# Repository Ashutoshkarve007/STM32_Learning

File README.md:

# STM32_Learning
 Learn STM32 together. 
 Create your name folder, >> create pull request.
 
#add to discord
webhook
lk

*Slave Board*

pin 1 - VCC     Modbus side
pin 2 - DO
pin 3 - CLK
pin 4 - rst*
pin 5 - GND

Master - Slave

Request Data - {slave_id, 0x06, CRC_L, CRC_H}

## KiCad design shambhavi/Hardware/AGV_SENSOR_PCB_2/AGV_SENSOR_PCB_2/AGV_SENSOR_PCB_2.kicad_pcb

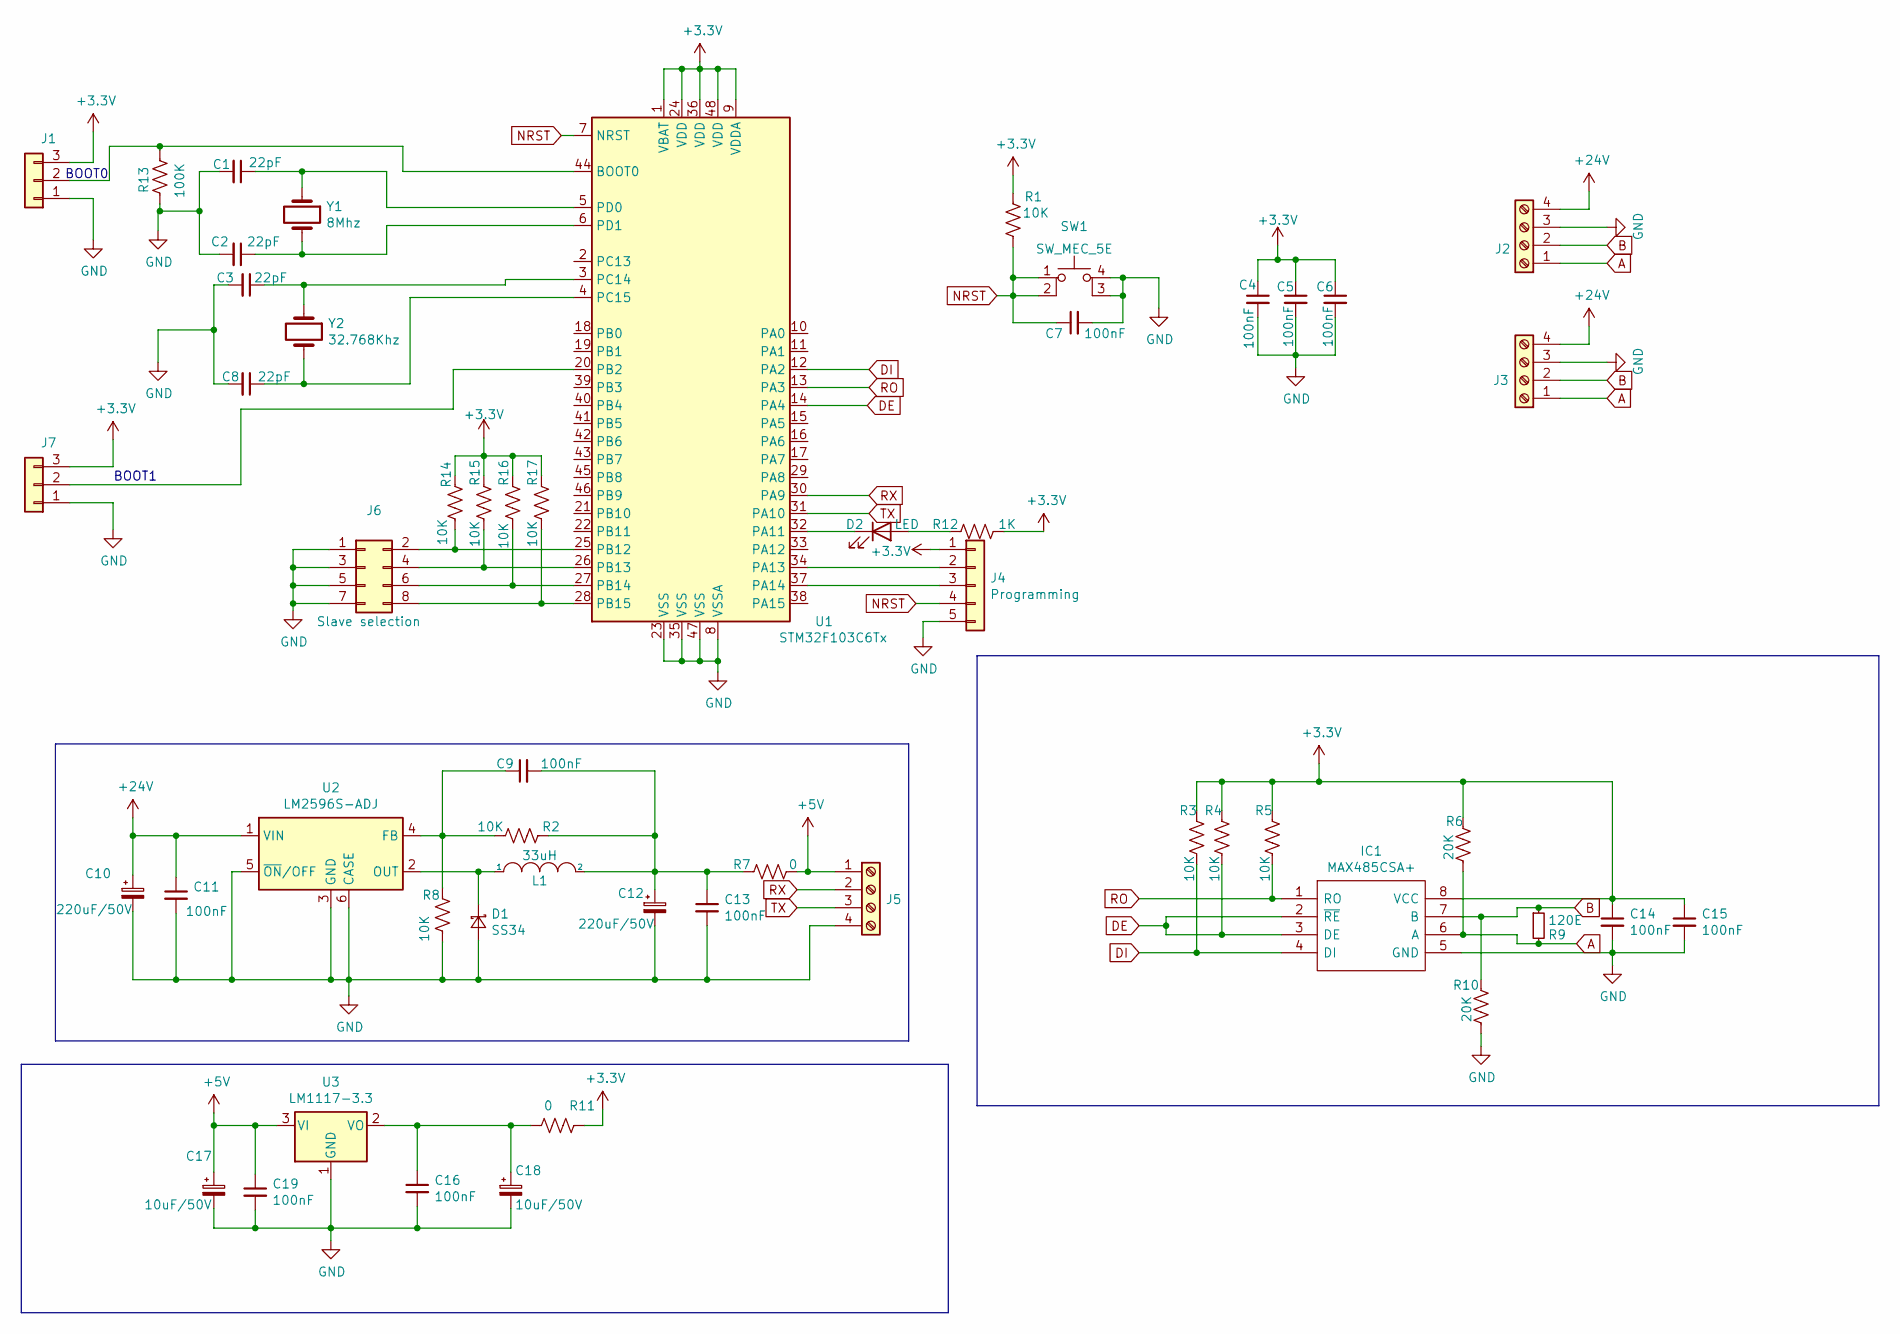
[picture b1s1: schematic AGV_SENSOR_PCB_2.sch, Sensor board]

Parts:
C1, C2, C3, C8: 22pF; C_0805_2012Metric
C4, C5, C6, C7, C9, C11, C13, C14, C15, C16, C19: 100nF; C_0805_2012Metric
C10, C12: 220uF/50V; CP_Radial_D8.0mm_P3.80mm
C17, C18: 10uF/50V; CP_Radial_D5.0mm_P2.50mm
D1: SS34; SODFL5226X100N
D2: LED; LED_0805_2012Metric
IC1: MAX485CSA+; SOIC127P600X175-8N; Manufacturer_Part_Number MAX485CSA+; Mouser Part Number 700-MAX485CSA
J1, J7: Conn_01x03; PinSocket_1x03_P2.54mm_Vertical
J2, J3, J5: Screw_Terminal_01x04; PhoenixContact_MCV_1,5_4-G-5.08_1x04_P5.08mm_Vertical
J4: Programming; PinSocket_1x05_P2.54mm_Vertical
J6: Slave selection; PinSocket_2x04_P2.54mm_Vertical
L1: 33uH; L_12x12mm_H6mm
R1, R2, R3, R4, R5, R8, R14, R15, R16, R17: 10K; R_0805_2012Metric
R6, R10: 20K; R_0805_2012Metric
R7, R11: 0; R_0805_2012Metric
R9: 120E; R_0805_2012Metric
R12: 1K; R_0805_2012Metric
R13: 100K; R_0805_2012Metric
SW1: SW_MEC_5E; SW_TH_Tactile_Omron_B3F-10xx
U1: STM32F103C6Tx; LQFP-48_7x7mm_P0.5mm
U2: LM2596S-ADJ; TO-263-5_TabPin3
U3: LM1117-3.3; SOT-223-3_TabPin2
Y1: 8Mhz; Crystal_HC49-4H_Vertical
Y2: 32.768Khz; Crystal_DS26_D2.0mm_L6.0mm_Horizontal

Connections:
+3V3: C4.1, C5.1, C6.1, C14.1, C15.1, IC1.8 (VCC), J1.3, J4.1, J7.3, R1.1, R3.1, R4.1, R5.1, R6.1, R11.1, R12.2, R14.1, R15.1, R16.1, R17.1, U1.1 (VBAT), U1.9 (VDDA), U1.24 (VDD), U1.36 (VDD), U1.48 (VDD)
+5V: C17.1, C19.1, J5.1, R7.1, U3.3 (VI)
+24V: C10.1, C11.1, J2.4, J3.4, U2.1 (VIN)
A: IC1.6 (A), J2.1, J3.1, R6.2, R9.2
B: IC1.7 (B), J2.2, J3.2, R9.1, R10.1
DE: IC1.2 (~RE), IC1.3 (DE), R4.2, U1.14 (PA4)
DI: IC1.4 (DI), R3.2, U1.12 (PA2)
GND: C1.2, C2.2, C3.2, C4.2, C5.2, C6.2, C7.2, C8.2, C10.2, C11.2, C12.2, C13.2, C14.2, C15.2, C16.2, C17.2, C18.2, C19.2, D1.1 (A), IC1.5 (GND), J1.1, J2.3, J3.3, J4.5, J5.4, J6.1, J6.3, J6.5, J6.7, J7.1, R8.1, R10.2, R13.1, SW1.3 (K), SW1.4 (A), U1.8 (VSSA), U1.23 (VSS), U1.35 (VSS), U1.47 (VSS), U2.3 (GND), U2.5 (~ON~/OFF), U2.6 (CASE), U3.1 (GND)
NRST: C7.1, J4.4, R1.2, SW1.1, SW1.2, U1.7 (NRST)
unnamed: C1.1, U1.5 (PD0), Y1.1
unnamed: C2.1, U1.6 (PD1), Y1.2
unnamed: C3.1, U1.3 (PC14), Y2.1
unnamed: C8.1, U1.4 (PC15), Y2.2
unnamed: C9.1, R2.2, R8.2, U2.4 (FB)
unnamed: C9.2, C12.1, C13.1, L1.2, R2.1, R7.2
unnamed: C16.1, C18.1, R11.2, U3.2 (VO)
unnamed: D1.2 (K), L1.1, U2.2 (OUT)
unnamed: D2.1 (K), U1.32 (PA11)
unnamed: D2.2 (A), R12.1
unnamed: J1.2, R13.2, U1.44 (BOOT0)
unnamed: J4.2, U1.34 (PA13)
unnamed: J4.3, U1.37 (PA14)
unnamed: J6.2, R14.2, U1.25 (PB12)
unnamed: J6.4, R15.2, U1.26 (PB13)
unnamed: J6.6, R16.2, U1.27 (PB14)
unnamed: J6.8, R17.2, U1.28 (PB15)
unnamed: J7.2, U1.20 (PB2)
RO: IC1.1 (RO), R5.2, U1.13 (PA3)
RX: J5.2, U1.30 (PA9)
TX: J5.3, U1.31 (PA10)

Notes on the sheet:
BOOT1
BOOT0

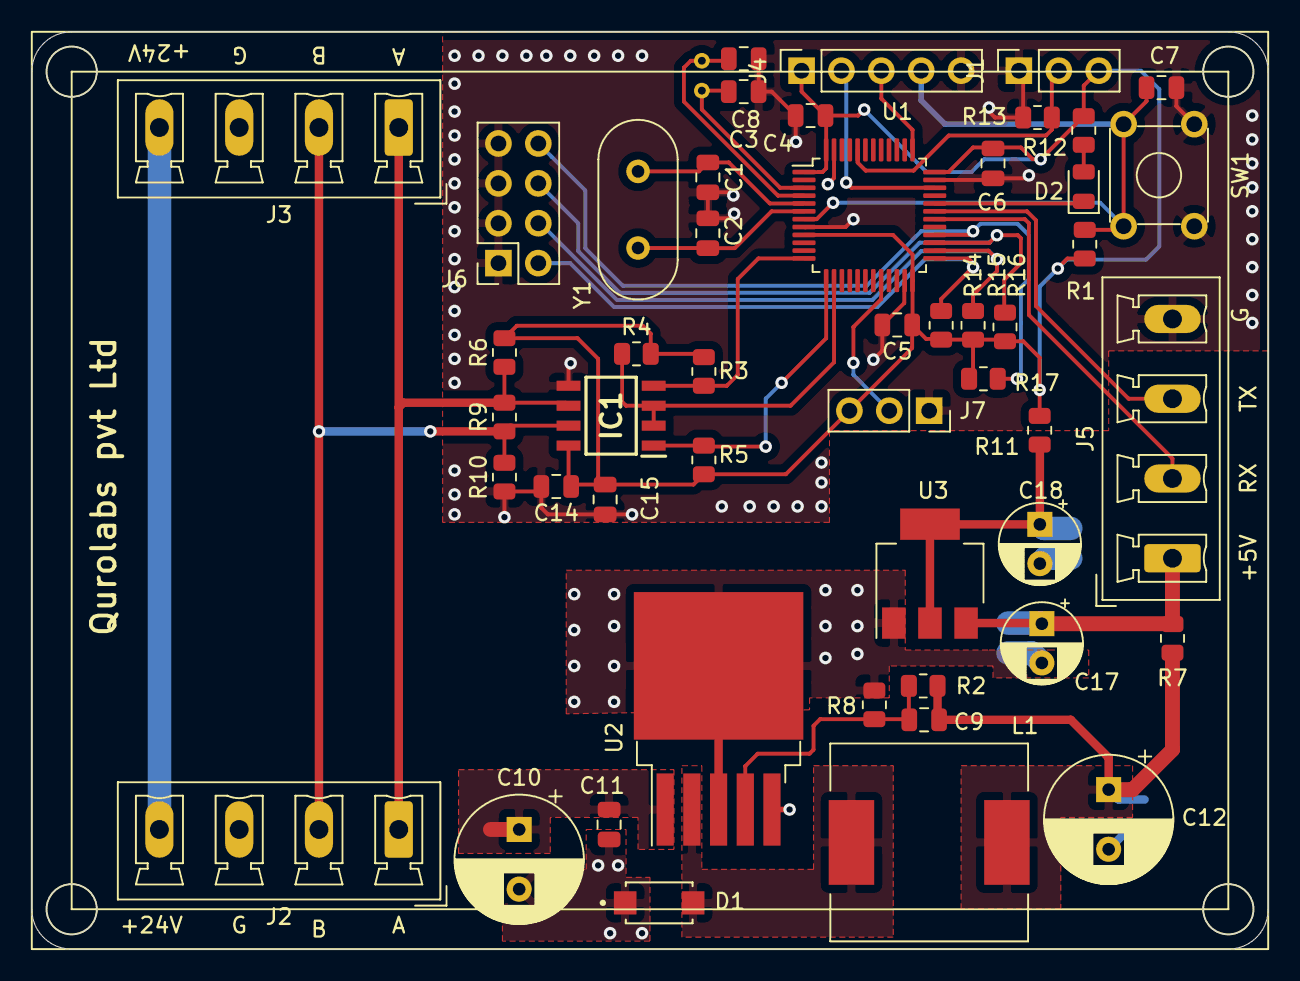
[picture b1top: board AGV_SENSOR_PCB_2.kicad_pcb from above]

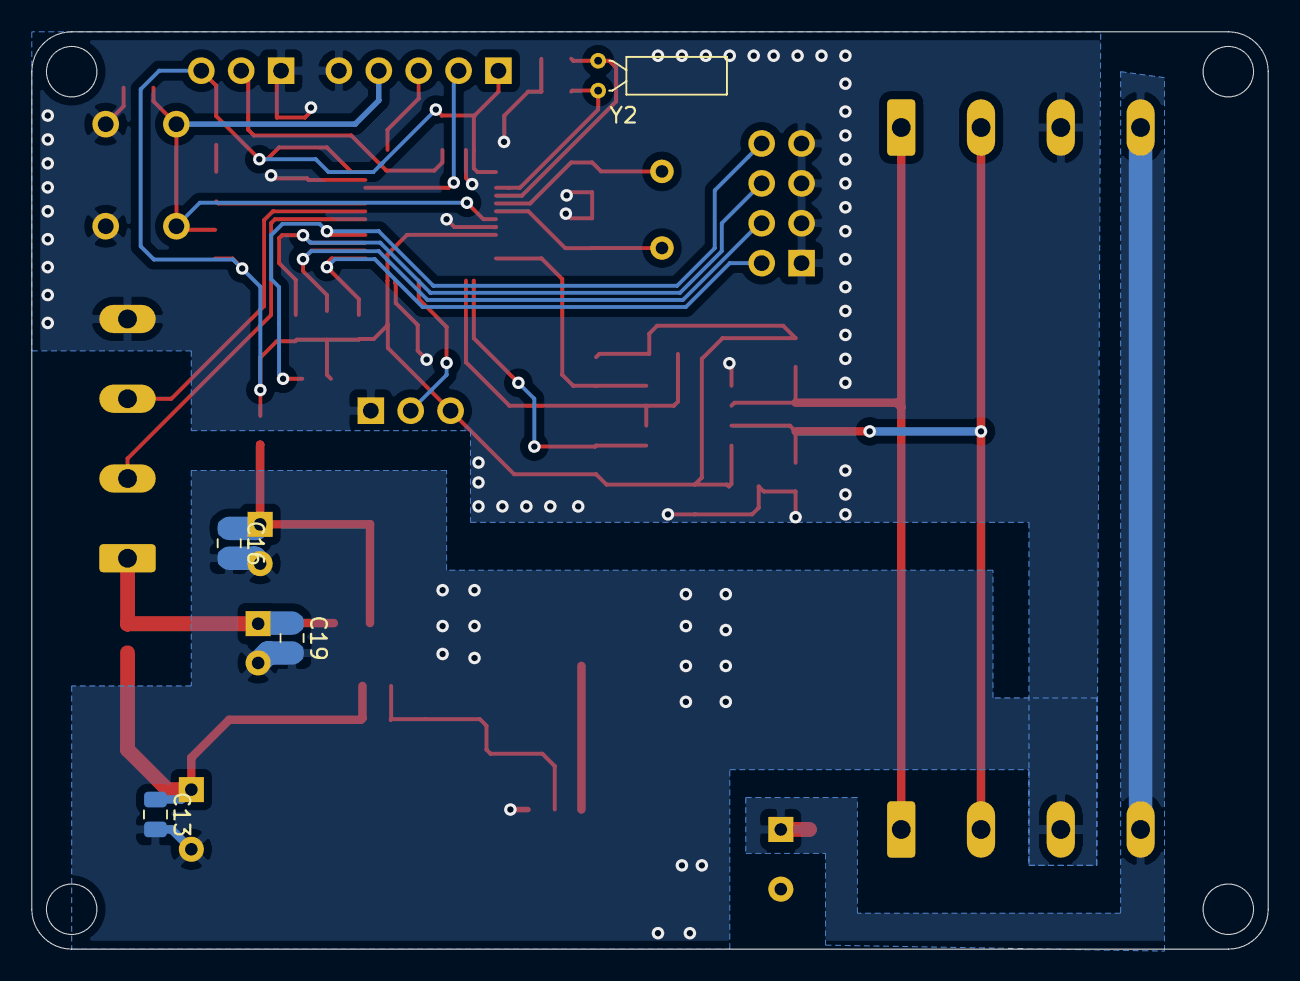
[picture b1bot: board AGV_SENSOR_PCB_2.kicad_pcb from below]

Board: 2 copper layers, 78.7 x 58.4 mm, 53 parts (4 on the bottom side), 30 nets.

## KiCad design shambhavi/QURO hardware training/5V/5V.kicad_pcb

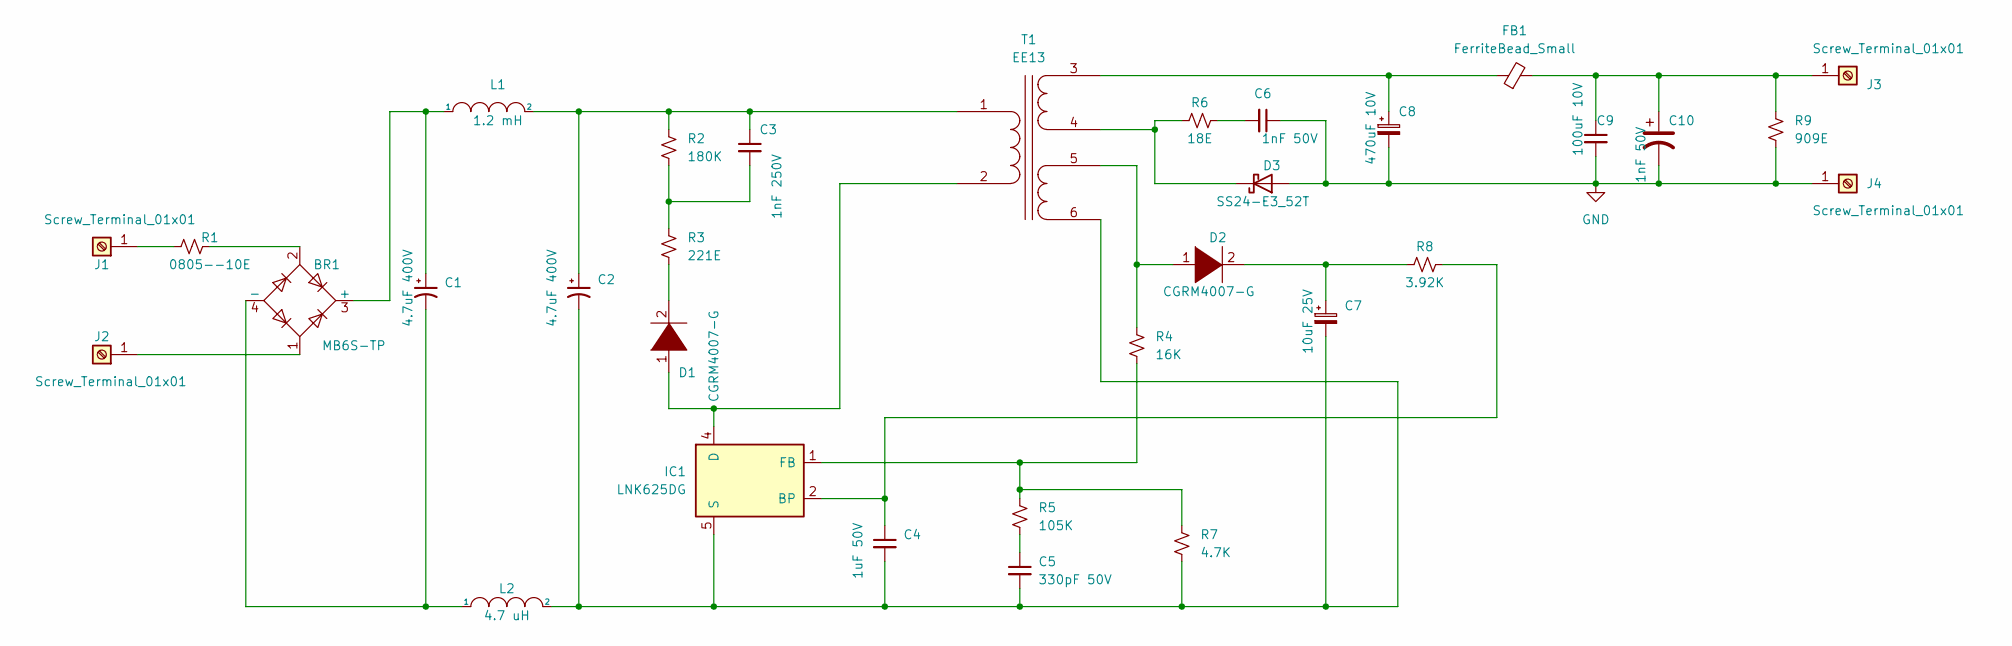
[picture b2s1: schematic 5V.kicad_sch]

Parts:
BR1: MB6S-TP; TO-269AA
C1: 4.7uF 400V; CP_Radial_D8.0mm_P3.80mm
C2: 4.7uF 400V; CP_Radial_D8.0mm_P3.50mm
C3: 1nF 250V; C_Radial_D8.0mm_H7.0mm_P3.50mm
C4: 1uF 50V; C_Radial_D8.0mm_H7.0mm_P3.50mm
C5: 330pF 50V; C_Radial_D8.0mm_H7.0mm_P3.50mm
C6: 1nF 50V; C_Radial_D8.0mm_H7.0mm_P3.50mm
C7: 10uF 25V; CP_Radial_D8.0mm_P3.50mm
C8: 470uF 10V; CP_Radial_D8.0mm_P3.50mm
C9: 100uF 10V; C_Radial_D8.0mm_H7.0mm_P3.50mm
C10: 1nF 50V; CP_Radial_D8.0mm_P3.80mm
D1, D2: CGRM4007-G; D_MiniMELF
D3: SS24-E3_52T; D_MiniMELF
FB1: FerriteBead_Small; L_0603_1608Metric
IC1: LNK625DG; PowerIntegrations_SO-8C
J1, J2, J3, J4: Screw_Terminal_01x01; TerminalBlock_MetzConnect_360272_1x01_Horizontal_ScrewM2.6
L1: 1.2 mH; L_Radial_D8.7mm_P5.00mm_Fastron_07HCP
L2: 4.7 uH; L_0805_2012Metric
R1: 0805--10E; R_0805_2012Metric_Pad1.20x1.40mm_HandSolder
R2: 180K; R_0805_2012Metric
R3: 221E; R_0805_2012Metric
R4: 16K; R_0815_2038Metric
R5: 105K; R_0815_2038Metric
R6: 18E; R_0815_2038Metric
R7: 4.7K; R_0815_2038Metric
R8: 3.92K; R_0815_2038Metric
R9: 909E; R_0815_2038Metric
T1: EE13; Transformer_Wuerth_750343373

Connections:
GND: C6.1, C8.2, C9.2, C10.2, D3.2 (A), J4.1, R9.2
unnamed: BR1.1, J2.1
unnamed: BR1.2, R1.2
unnamed: BR1.3 (+), C1.1, L1.1
unnamed: BR1.4 (-), C1.2, L2.1
unnamed: C2.1, C3.1, L1.2, R2.1, T1.1 (AA)
unnamed: C2.2, C4.2, C5.2, C7.2, IC1.5 (S), IC1.6 (S), IC1.7 (S), IC1.8 (S), L2.2, R7.2, T1.6 (SD)
unnamed: C5.1, R5.2
unnamed: C6.2, R6.2
unnamed: C8.1, FB1.1, T1.3 (SA)
unnamed: D1.1 (K), IC1.4 (D), T1.2 (AB)
unnamed: D1.2 (A), R3.2
unnamed: C7.1, D2.2 (A), R8.1
unnamed: IC1.1 (FB), R4.2, R5.1, R7.1
unnamed: C4.1, IC1.2 (BP), R8.2
unnamed: C9.1, C10.1, FB1.2, J3.1, R9.1
unnamed: J1.1, R1.1
unnamed: C3.2, R2.2, R3.1
unnamed: D2.1 (K), R4.1, T1.5 (SC)
unnamed: D3.1 (K), R6.1, T1.4 (SB)

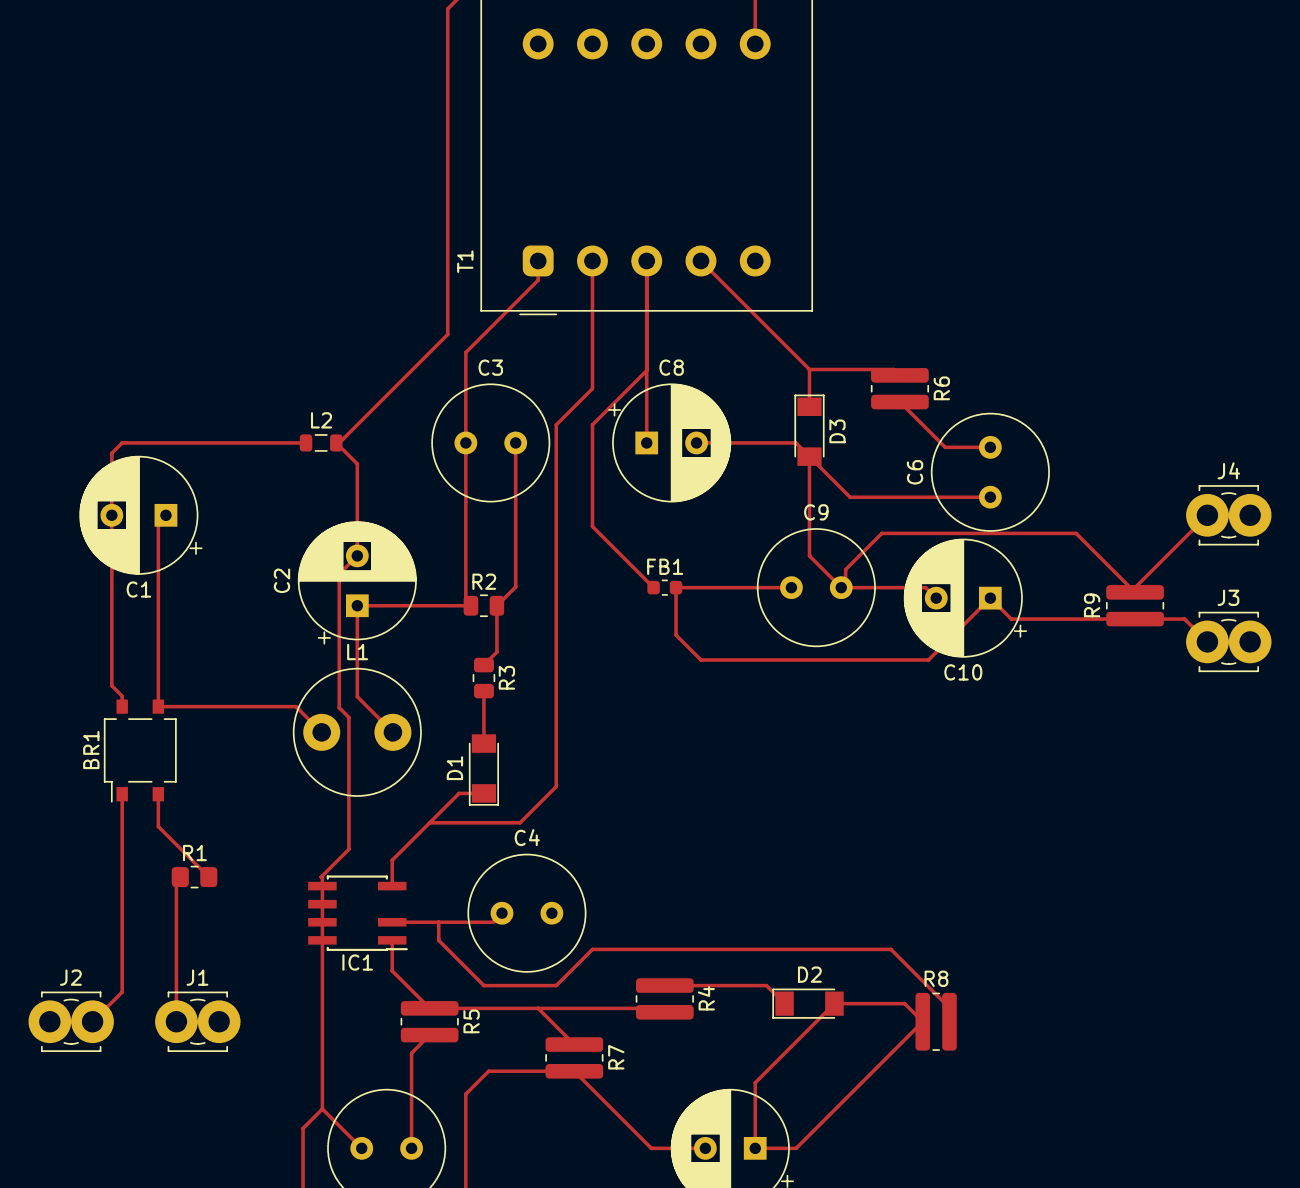
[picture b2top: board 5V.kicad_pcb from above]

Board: 2 copper layers, 32 parts (0 on the bottom side), 20 nets.

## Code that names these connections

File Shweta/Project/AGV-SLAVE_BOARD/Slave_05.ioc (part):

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Mcu.Name=STM32F103C(4-6)Tx
Mcu.Package=LQFP48
Mcu.UserName=STM32F103C6Tx
PA10.Mode=Asynchronous
PA10.Signal=USART1_RX
PA11.GPIOParameters=GPIO_Label
PA11.GPIO_Label=LED1
PA11.Signal=GPIO_Output
PA13.Mode=Serial_Wire
PA13.Signal=SYS_JTMS-SWDIO
PA14.Mode=Serial_Wire
PA14.Signal=SYS_JTCK-SWCLK
PA2.GPIOParameters=GPIO_Label
PA2.GPIO_Label=MAX3485_DI
PA2.Mode=Asynchronous
PA2.Signal=USART2_TX
PA3.GPIOParameters=GPIO_Label
PA3.GPIO_Label=MAX3485_RO
PA3.Mode=Asynchronous
PA3.Signal=USART2_RX
PA4.GPIOParameters=GPIO_Label
PA4.GPIO_Label=MAX3485_DE
PA4.Signal=GPIO_Output
PA9.Mode=Asynchronous
PA9.Signal=USART1_TX
PB12.GPIOParameters=GPIO_Label
PB12.GPIO_Label=ID_PIN_1
PB12.Signal=GPIO_Input
PB13.GPIOParameters=GPIO_Label
PB13.GPIO_Label=ID_PIN_2
PB13.Signal=GPIO_Input
PB14.GPIOParameters=GPIO_Label
PB14.GPIO_Label=ID_PIN_3
PB14.Signal=GPIO_Input
PB15.GPIOParameters=GPIO_Label
PB15.GPIO_Label=ID_PIN_4
PB15.Signal=GPIO_Input
PC14-OSC32_IN.Mode=LSE-External-Oscillator
PC14-OSC32_IN.Signal=RCC_OSC32_IN
PC15-OSC32_OUT.Mode=LSE-External-Oscillator
PC15-OSC32_OUT.Signal=RCC_OSC32_OUT
PD0-OSC_IN.Mode=HSE-External-Oscillator
PD0-OSC_IN.Signal=RCC_OSC_IN
PD1-OSC_OUT.Mode=HSE-External-Oscillator
PD1-OSC_OUT.Signal=RCC_OSC_OUT
RCC.SYSCLKFreq_VALUE=72000000
RCC.SYSCLKSource=RCC_SYSCLKSOURCE_PLLCLK
board=custom

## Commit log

2022-09-13 id_detect_program
2022-09-13 upload Id_detect
2022-09-13 id_detect
2022-09-13 slave_id
2022-09-13 dummy_master_project
2022-09-13 dummymaster function file
2022-09-13 crc prog
2022-09-13 crc build
2022-09-13 crc c file created
2022-09-13 update changes
2022-09-13 Transmitting Master data from UART
2022-09-13 splitting Methods
2022-09-13 Transmitting on Modbus from master to slave
2022-09-13 SLAVE_Sensor_Board Project
2022-09-13 slave.c and slave.h file added to Project
2022-09-13 slave id
2022-09-13 CRC Check function done
2022-09-13 Modbus crc and slave id verify
2022-09-13 multi uart
2022-09-14 build
2022-09-14 slavedata function
2022-09-14 Slave Device program Transmission with packet
2022-09-14 Slave Final program test01
2022-09-15 Slave error code
2022-09-15 test build
2022-09-15 DE pin high code to send data on MODBUS
2022-09-15 slave Modbus transmission DMA Code
2022-09-17 update new project
2022-09-19 AGV Final
2022-09-21 Timer Intrrupt.
2022-09-22 folder created
2022-09-22 draw.io
2022-09-22 blockdiagram
2022-09-22 created readme file
2022-09-23 IMAGE
2022-09-23 level sensor
2022-09-23 level sensor update
2022-09-23 Rename ReadMe.txt to imp.md
2022-09-24 updated folder
2022-09-26 Rename modbus.md to modbus.c
2022-10-17 edited read me
2022-10-18 slave Board
2022-10-19 sd card progrAM
2022-10-19 sd_card update
2022-10-19 upload
2022-10-20 sd card update
2022-10-20 bug fix
2022-10-20 trial
2022-10-21 rf project
2022-10-22 AGV hardware
2022-10-22 hx711 final
2022-10-22 SD_Card
2022-11-03 final
2022-12-05 rma project
2022-12-12 accelerometer and zigbee
2023-01-28 lora_project
2023-02-18 flash update
